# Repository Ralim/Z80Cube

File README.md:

# Z80Cube - Project Zeta
A 5 layer 5cm * 5cm cubish shaped z80 machine
Basically designed as a learning experience.
Big difference from other builds I have seen is the entire system runs on a 64K memory space of ram, and the atmega2560 pre-load's the bootloader into the chip on system startup.
This bootloader for the z80 then allows the user to test memory and load + execute programs.

## Layers
* Bus Display ->Led indicators for the bus
* Z80 CPU
* 64K SRAM/ROM
* Power and Programmer (Atmega 2560+flash storage to store the software)

##ToDo:
Basically everything
* Build PCBs
* Test PCBs
* Write the code for the bootloader (Going to use Arduino to keep it easy for others)
* Write arduino code for storing program packages
* Write arduino code for monitoring the bus
* write arduino code for single stepping operation

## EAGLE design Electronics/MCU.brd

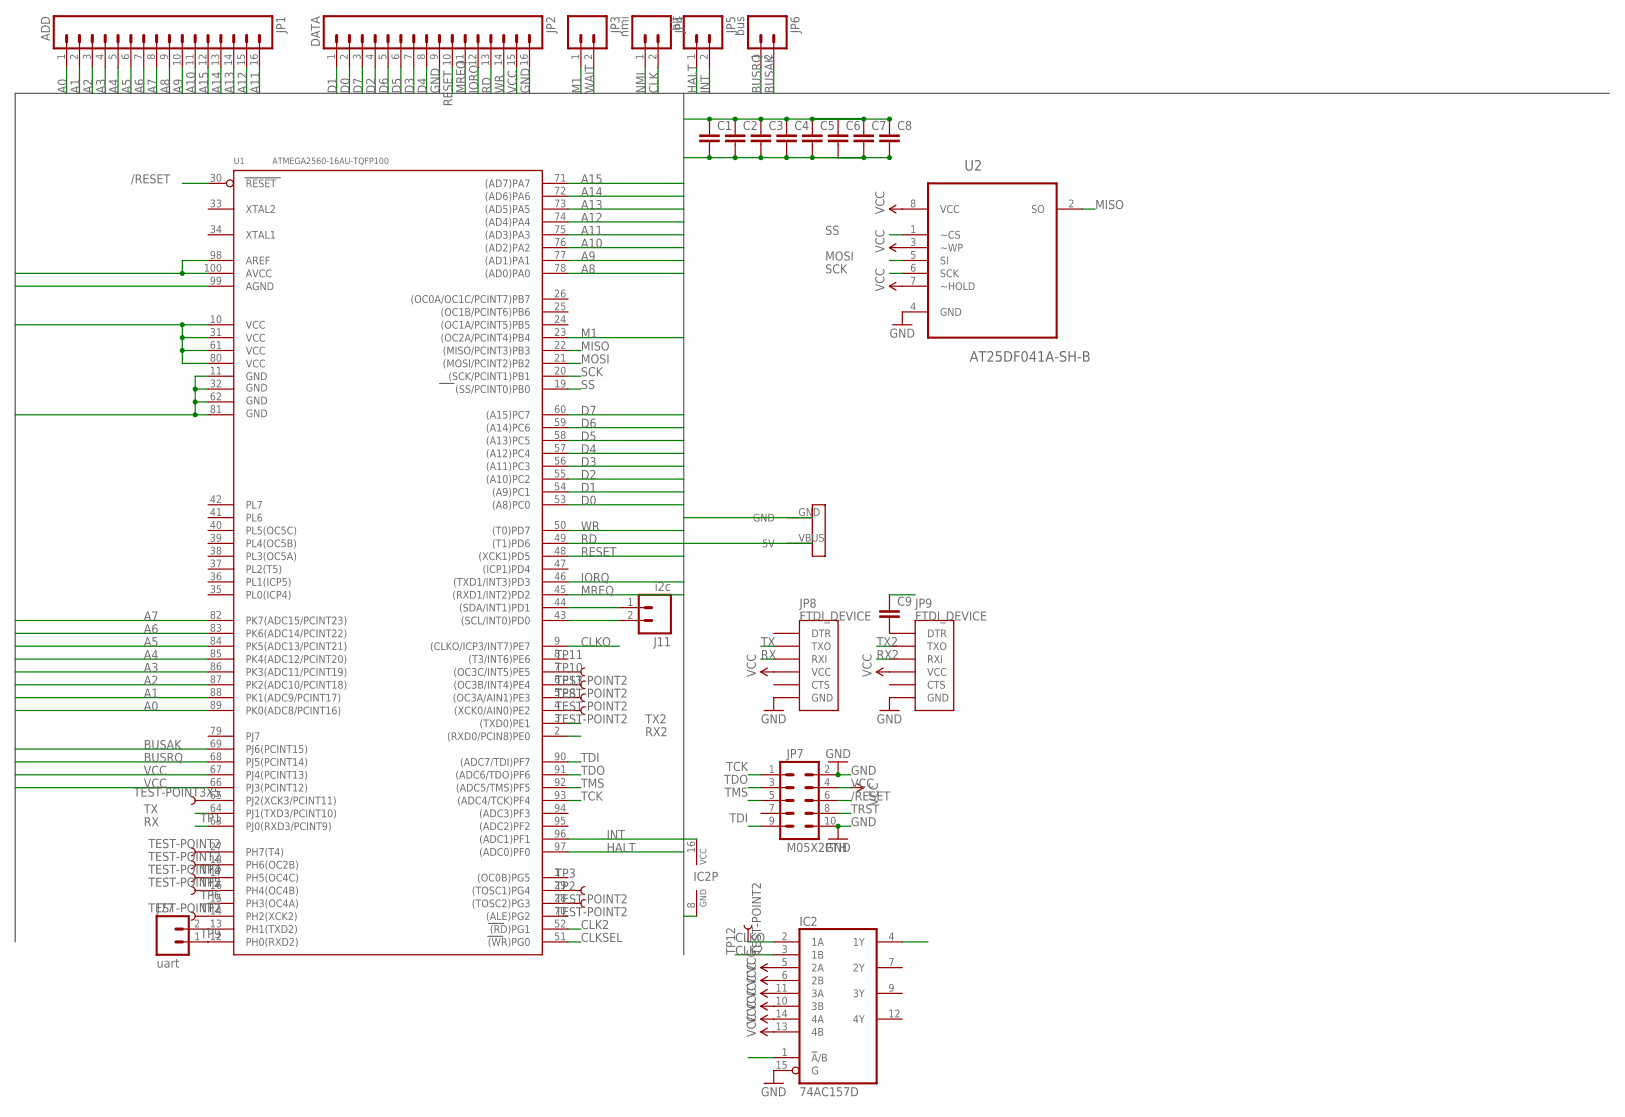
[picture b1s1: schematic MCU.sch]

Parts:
C1, C2, C3, C4, C5, C6, C7, C8, C9: C-EUC0805; C0805
IC2: 74AC157D; SO16
J11: i2c; 1X02
J77: uart; 1X02
JP1: ADD; 1X16
JP2: DATA; 1X16
JP3: M02PTH; 1X02
JP4: nmi; 1X02
JP5: hlt; 1X02
JP6: bus; 1X02
JP7: M05X2PTH; AVR_ICSP
JP8, JP9: FTDI_DEVICE; FTDI_DEVICE_SIDE
TP1: TEST-POINT3X5; PAD.03X.05
TP2, TP3, TP4, TP5, TP6, TP7, TP8, TP9, TP10, TP11, TP12, TP13: TEST-POINT2; PAD.02X.02
U1: ATMEGA2560-16AU-TQFP100; TQFP100-0.5-14X14MM
U2: AT25DF041A-SH-B; SOIC127P798X216-8N
U$1: USB-MICRO-PWR; USB-MICROB-PWR

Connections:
/RESET: C9.1, JP7.6, U1.30 (RESET)
A0: JP1.1, U1.89 (PK0(ADC8/PCINT16))
A1: JP1.2, U1.88 (PK1(ADC9/PCINT17))
A2: JP1.3, U1.87 (PK2(ADC10/PCINT18))
A3: JP1.4, U1.86 (PK3(ADC11/PCINT19))
A4: JP1.5, U1.85 (PK4(ADC12/PCINT20))
A5: JP1.6, U1.84 (PK5(ADC13/PCINT21))
A6: JP1.7, U1.83 (PK6(ADC14/PCINT22))
A7: JP1.8, U1.82 (PK7(ADC15/PCINT23))
A8: JP1.9, U1.78 ((AD0)PA0)
A9: JP1.10, U1.77 ((AD1)PA1)
A10: JP1.11, U1.76 ((AD2)PA2)
A11: JP1.16, U1.75 ((AD3)PA3)
A12: JP1.15, U1.74 ((AD4)PA4)
A13: JP1.14, U1.73 ((AD5)PA5)
A14: JP1.13, U1.72 ((AD6)PA6)
A15: JP1.12, U1.71 ((AD7)PA7)
BUSAK: JP6.2, U1.69 (PJ6(PCINT15))
BUSRQ: JP6.1, U1.68 (PJ5(PCINT14))
CLK: IC2.4 (1Y), JP4.2
CLK2: IC2.3 (1B), U1.52 ((RD)PG1)
CLKO: IC2.2 (1A), TP12.P$1, U1.9 ((CLKO/ICP3/INT7)PE7)
CLKSEL: IC2.1 (!A!/B), U1.51 ((WR)PG0)
D0: JP2.2, U1.53 ((A8)PC0)
D1: JP2.1, U1.54 ((A9)PC1)
D2: JP2.4, U1.55 ((A10)PC2)
D3: JP2.7, U1.56 ((A11)PC3)
D4: JP2.8, U1.57 ((A12)PC4)
D5: JP2.6, U1.58 ((A13)PC5)
D6: JP2.5, U1.59 ((A14)PC6)
D7: JP2.3, U1.60 ((A15)PC7)
GND: C1.2, C2.2, C3.2, C4.2, C5.2, C6.2, C7.2, C8.2, IC2.8 (GND), IC2.15 (G), JP2.9, JP2.16, JP7.2, JP7.10, JP8.P$6 (GND), JP9.P$6 (GND), U1.11 (GND), U1.32 (GND1), U1.62 (GND2), U1.81 (GND3), U1.99 (AGND), U2.4 (GND), U$1.GND
HALT: JP5.1, U1.97 ((ADC0)PF0)
INT: JP5.2, U1.96 ((ADC1)PF1)
IORQ: JP2.12, U1.46 ((TXD1/INT3)PD3)
M1: JP3.1, U1.23 ((OC2A/PCINT4)PB4)
MISO: U1.22 ((MISO/PCINT3)PB3), U2.2 (SO)
MOSI: U1.21 ((MOSI/PCINT2)PB2), U2.5 (SI)
MREQ: JP2.11, U1.45 ((RXD1/INT2)PD2)
unnamed: J77.1, U1.12 (PH0(RXD2))
unnamed: J77.2, U1.13 (PH1(TXD2))
unnamed: J11.1, U1.44 ((SDA/INT1)PD1)
unnamed: J11.2, U1.43 ((SCL/INT0)PD0)
unnamed: TP1.P$1, U1.65 (PJ2(XCK3/PCINT11))
unnamed: TP2.P$1, U1.28 ((TOSC2)PG3)
unnamed: TP3.P$1, U1.29 ((TOSC1)PG4)
unnamed: TP4.P$1, U1.27 (PH7(T4))
unnamed: TP5.P$1, U1.18 (PH6(OC2B))
unnamed: TP6.P$1, U1.17 (PH5(OC4C))
unnamed: TP7.P$1, U1.16 (PH4(OC4B))
unnamed: TP8.P$1, U1.4 ((XCK0/AIN0)PE2)
unnamed: TP9.P$1, U1.14 (PH2(XCK2))
unnamed: TP10.P$1, U1.6 ((OC3B/INT4)PE4)
unnamed: TP11.P$1, U1.7 ((OC3C/INT5)PE5)
unnamed: C9.2, JP9.P$1 (DTR)
unnamed: TP13.P$1, U1.5 ((OC3A/AIN1)PE3)
NMI: JP4.1
RD: JP2.13, U1.49 ((T1)PD6)
RESET: JP2.10, U1.48 ((XCK1)PD5)
RX: JP8.P$3 (RXI), U1.63 (PJ0(RXD3/PCINT9))
RX2: JP9.P$3 (RXI), U1.2 ((RXD0/PCIN8)PE0)
SCK: U1.20 ((SCK/PCINT1)PB1), U2.6 (SCK)
SS: U1.19 ((SS/PCINT0)PB0), U2.1 (~CS)
TCK: JP7.1, U1.93 ((ADC4/TCK)PF4)
TDI: JP7.9, U1.90 ((ADC7/TDI)PF7)
TDO: JP7.3, U1.91 ((ADC6/TDO)PF6)
TMS: JP7.5, U1.92 ((ADC5/TMS)PF5)
TRST: JP7.8
TX: JP8.P$2 (TXO), U1.64 (PJ1(TXD3/PCINT10))
TX2: JP9.P$2 (TXO), U1.3 ((TXD0)PE1)
VCC: C1.1, C2.1, C3.1, C4.1, C5.1, C6.1, C7.1, C8.1, IC2.5 (2A), IC2.6 (2B), IC2.10 (3B), IC2.11 (3A), IC2.13 (4B), IC2.14 (4A), IC2.16 (VCC), JP2.15, JP7.4, JP8.P$4 (VCC), JP9.P$4 (VCC), U1.10 (VCC), U1.31 (VCC1), U1.61 (VCC2), U1.66 (PJ3(PCINT12)), U1.67 (PJ4(PCINT13)), U1.80 (VCC3), U1.98 (AREF), U1.100 (AVCC), U2.3 (~WP), U2.7 (~HOLD), U2.8 (VCC), U$1.VBUS (5V)
WAIT: JP3.2
WR: JP2.14, U1.50 ((T0)PD7)

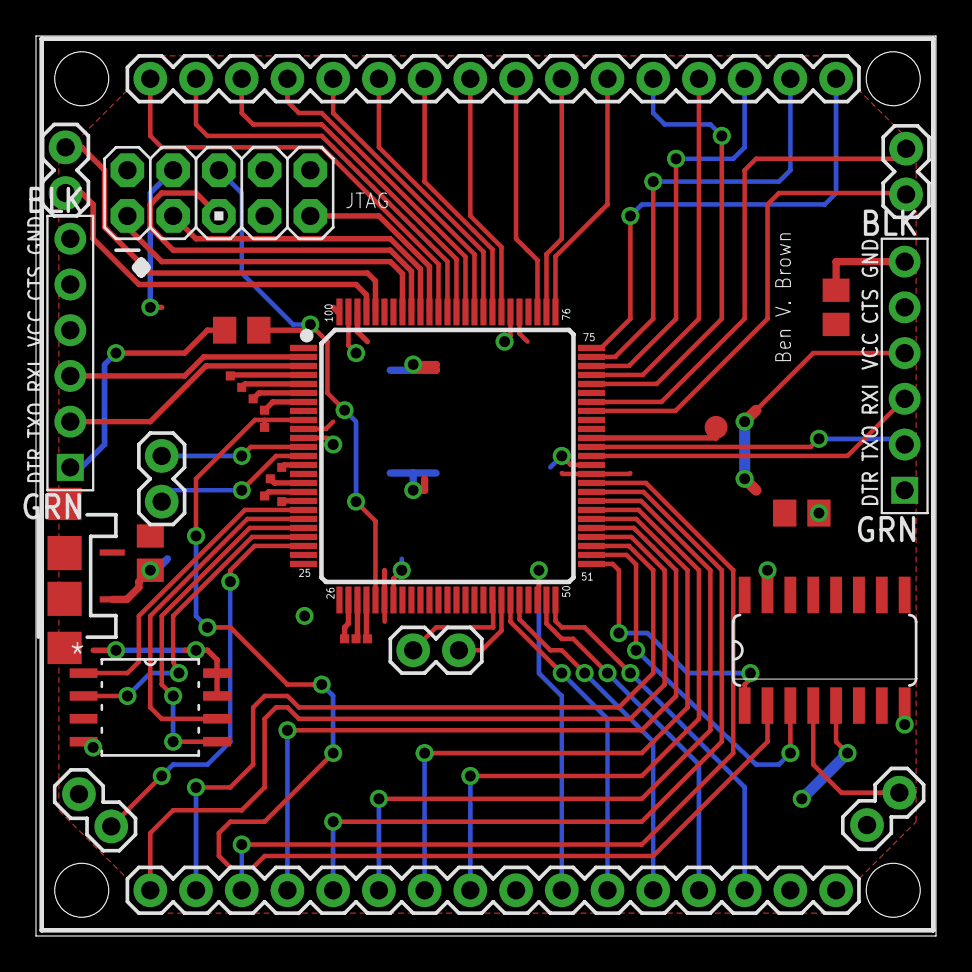
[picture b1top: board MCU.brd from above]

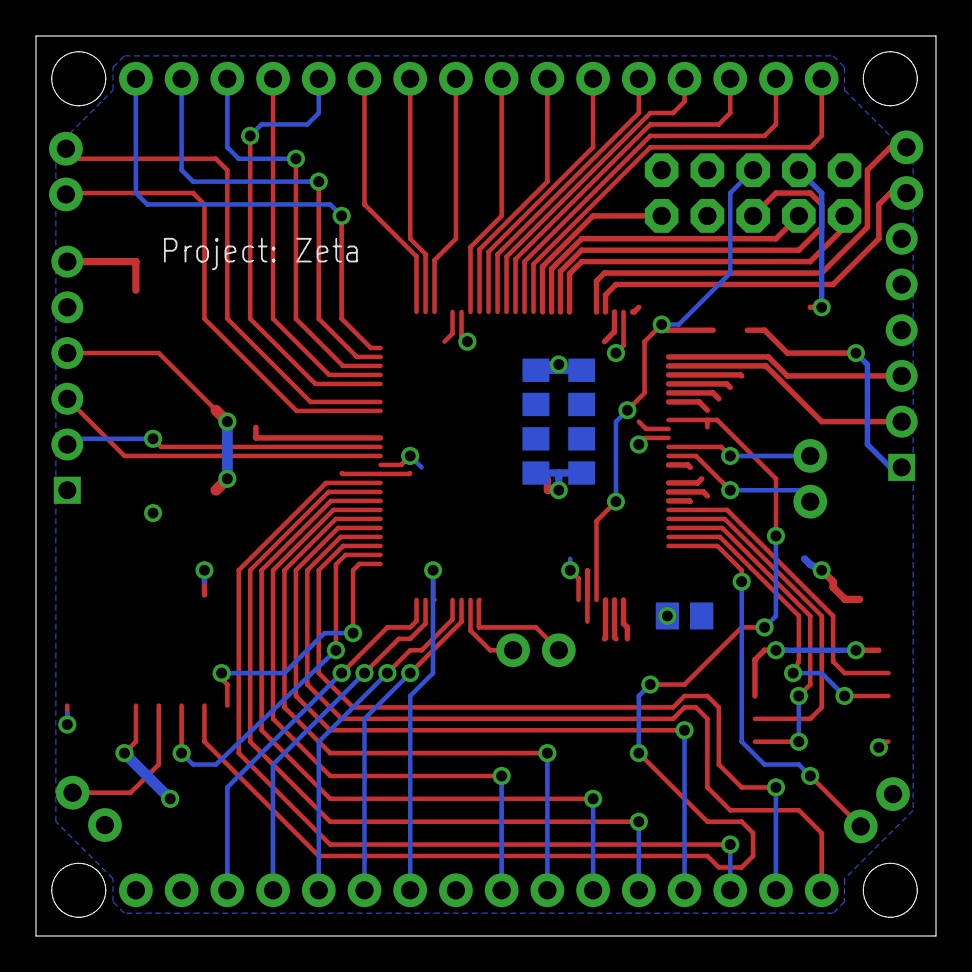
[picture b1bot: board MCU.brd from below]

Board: 2 copper layers, 50.0 x 50.0 mm, 37 parts (5 on the bottom side), 70 nets.

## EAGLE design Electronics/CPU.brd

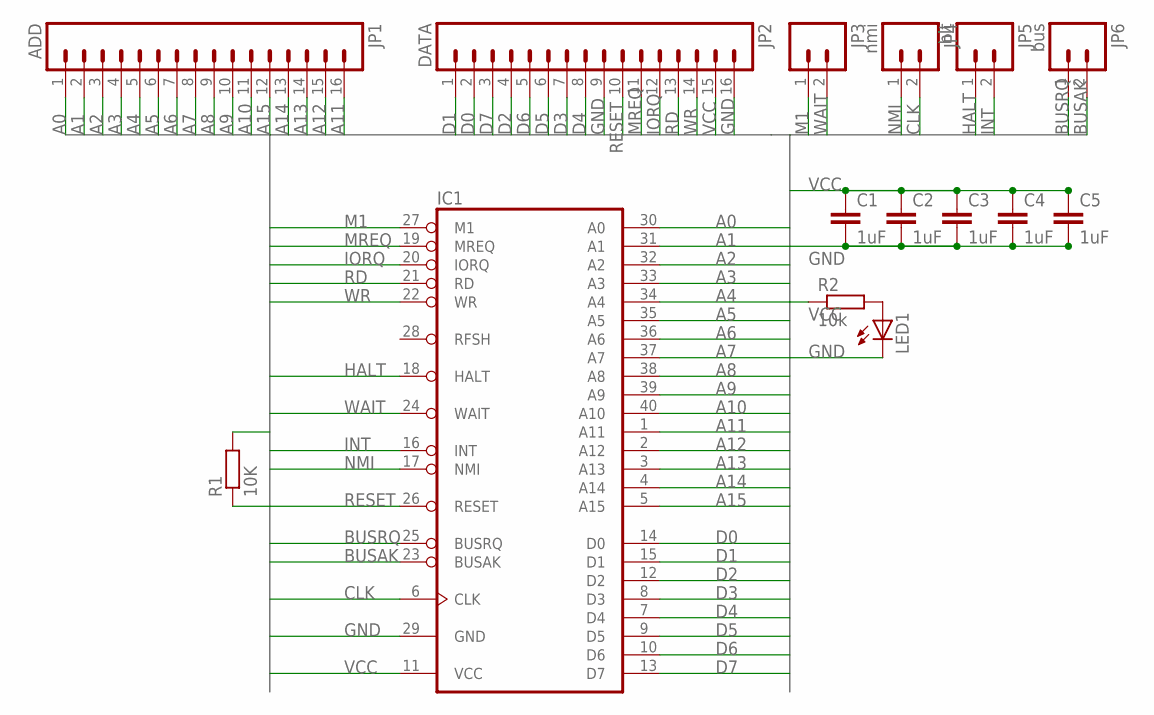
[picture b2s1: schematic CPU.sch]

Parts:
C1, C2, C3, C4, C5: 1uF; C0805
IC1: Z80CPU; DIL40
JP1: ADD; 1X16
JP2: DATA; 1X16
JP3: M02PTH; 1X02
JP4: nmi; 1X02
JP5: hlt; 1X02
JP6: bus; 1X02
LED1: LEDCHIP-LED0805; CHIP-LED0805
R1: 10K; M0805
R2: 10k; M0805

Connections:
A0: IC1.30 (A0), JP1.1
A1: IC1.31 (A1), JP1.2
A2: IC1.32 (A2), JP1.3
A3: IC1.33 (A3), JP1.4
A4: IC1.34 (A4), JP1.5
A5: IC1.35 (A5), JP1.6
A6: IC1.36 (A6), JP1.7
A7: IC1.37 (A7), JP1.8
A8: IC1.38 (A8), JP1.9
A9: IC1.39 (A9), JP1.10
A10: IC1.40 (A10), JP1.11
A11: IC1.1 (A11), JP1.16
A12: IC1.2 (A12), JP1.15
A13: IC1.3 (A13), JP1.14
A14: IC1.4 (A14), JP1.13
A15: IC1.5 (A15), JP1.12
BUSAK: IC1.23 (BUSAK), JP6.2
BUSRQ: IC1.25 (BUSRQ), JP6.1
CLK: IC1.6 (CLK), JP4.2
D0: IC1.14 (D0), JP2.2
D1: IC1.15 (D1), JP2.1
D2: IC1.12 (D2), JP2.4
D3: IC1.8 (D3), JP2.7
D4: IC1.7 (D4), JP2.8
D5: IC1.9 (D5), JP2.6
D6: IC1.10 (D6), JP2.5
D7: IC1.13 (D7), JP2.3
GND: C1.2, C2.2, C3.2, C4.2, C5.2, IC1.29 (GND), JP2.9, JP2.16, LED1.C
HALT: IC1.18 (HALT), JP5.1
INT: IC1.16 (INT), JP5.2
IORQ: IC1.20 (IORQ), JP2.12
M1: IC1.27 (M1), JP3.1
MREQ: IC1.19 (MREQ), JP2.11
unnamed: LED1.A, R2.2
NMI: IC1.17 (NMI), JP4.1
RD: IC1.21 (RD), JP2.13
RESET: IC1.26 (RESET), JP2.10, R1.1
VCC: C1.1, C2.1, C3.1, C4.1, C5.1, IC1.11 (VCC), JP2.15, R1.2, R2.1
WAIT: IC1.24 (WAIT), JP3.2
WR: IC1.22 (WR), JP2.14

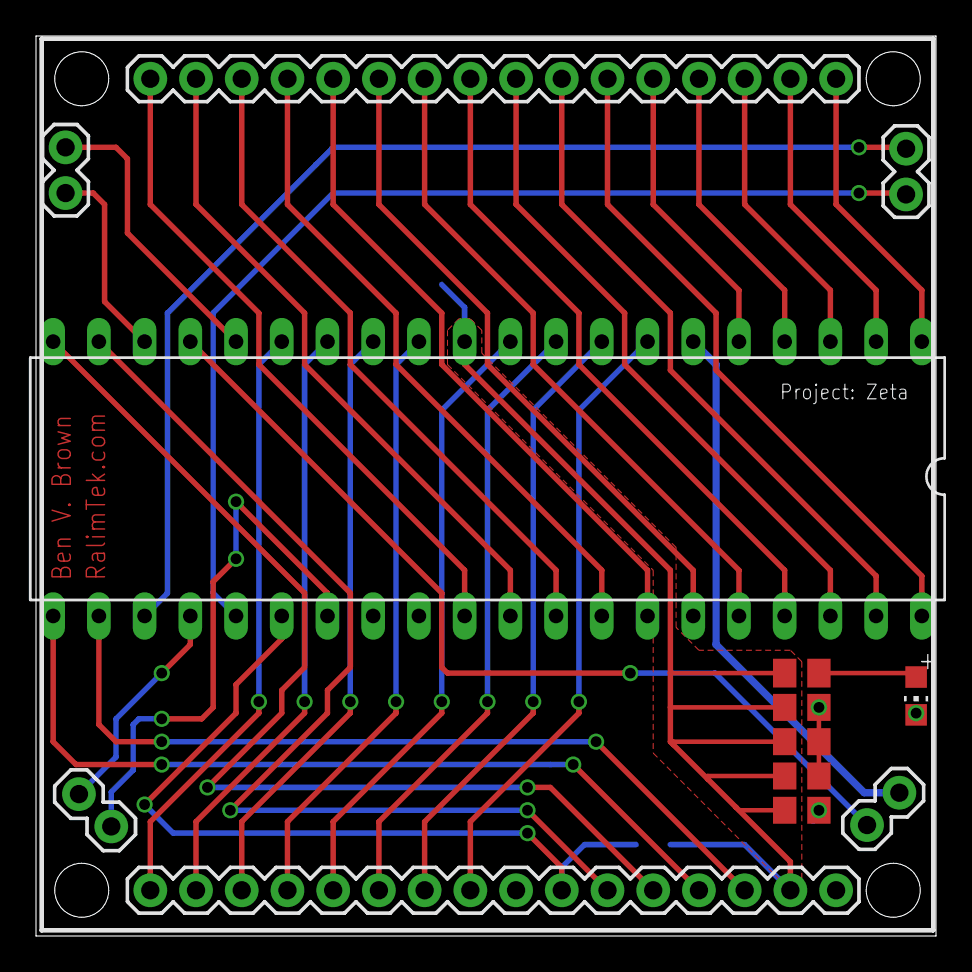
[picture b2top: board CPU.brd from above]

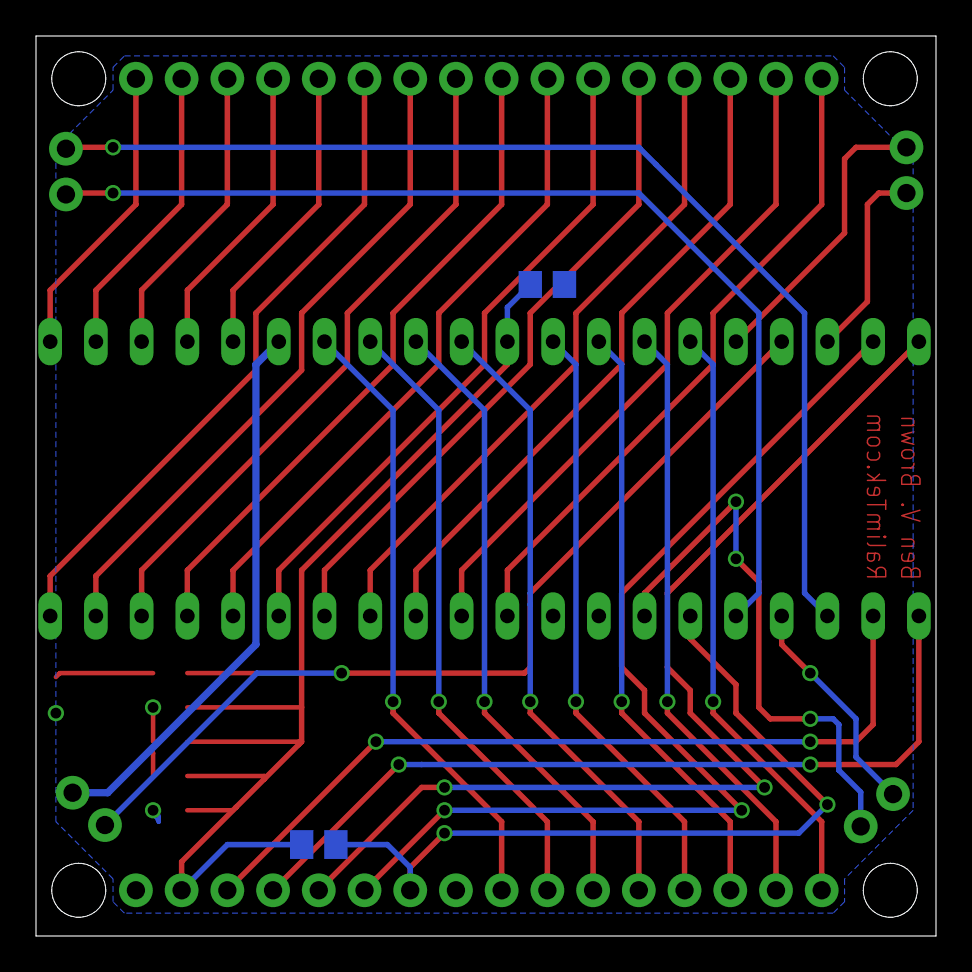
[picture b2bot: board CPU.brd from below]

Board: 2 copper layers, 50.0 x 50.0 mm, 15 parts (2 on the bottom side), 40 nets.

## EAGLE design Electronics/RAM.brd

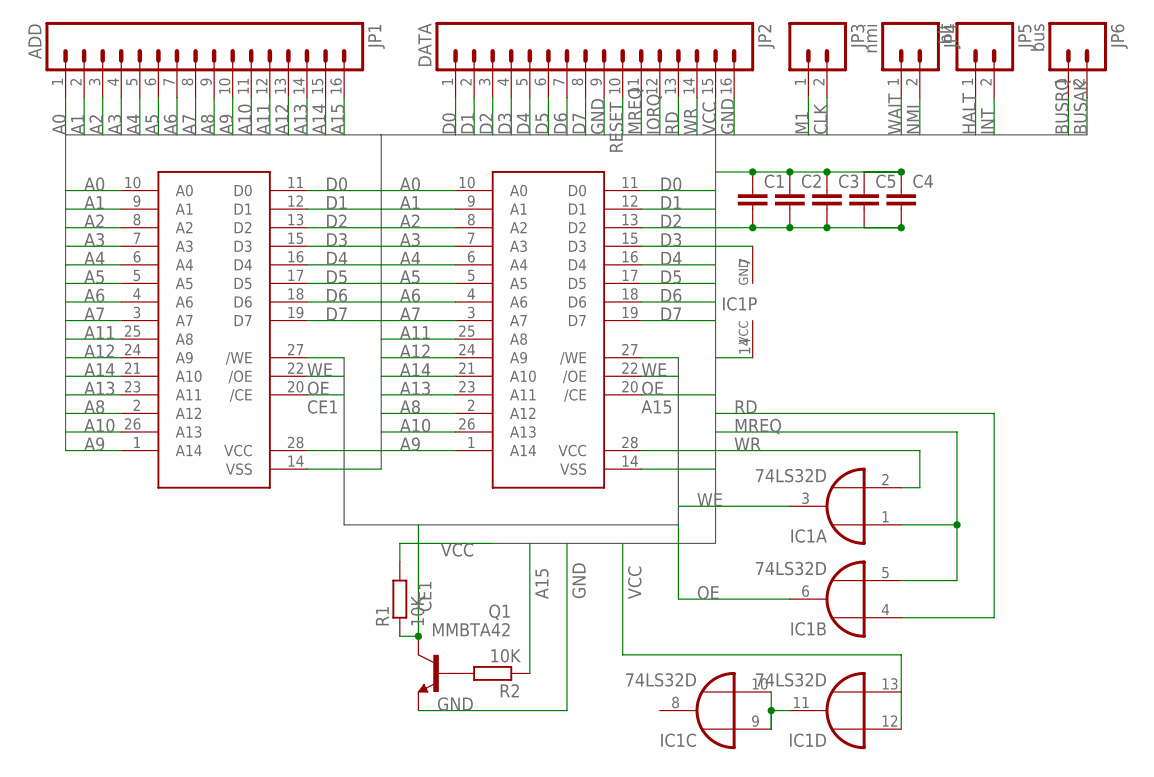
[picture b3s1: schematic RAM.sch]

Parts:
C1, C2, C3, C4, C5: C-EUC0805; C0805
IC1: 74LS32D; SO14
JP1: ADD; 1X16
JP2: DATA; 1X16
JP3: M02PTH; 1X02
JP4: nmi; 1X02
JP5: hlt; 1X02
JP6: bus; 1X02
Q1: MMBTA42; SOT23
R1, R2: 10K; M0805
U$1, U$2: AS7C256; SOP28

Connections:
A0: JP1.1, U$1.10 (A0), U$2.10 (A0)
A1: JP1.2, U$1.9 (A1), U$2.9 (A1)
A2: JP1.3, U$1.8 (A2), U$2.8 (A2)
A3: JP1.4, U$1.7 (A3), U$2.7 (A3)
A4: JP1.5, U$1.6 (A4), U$2.6 (A4)
A5: JP1.6, U$1.5 (A5), U$2.5 (A5)
A6: JP1.7, U$1.4 (A6), U$2.4 (A6)
A7: JP1.8, U$1.3 (A7), U$2.3 (A7)
A8: JP1.9, U$1.2 (A12), U$2.2 (A12)
A9: JP1.10, U$1.1 (A14), U$2.1 (A14)
A10: JP1.11, U$1.26 (A13), U$2.26 (A13)
A11: JP1.12, U$1.25 (A8), U$2.25 (A8)
A12: JP1.13, U$1.24 (A9), U$2.24 (A9)
A13: JP1.14, U$1.23 (A11), U$2.23 (A11)
A14: JP1.15, U$1.21 (A10), U$2.21 (A10)
A15: JP1.16, R2.1, U$2.20 (/CE)
BUSAK: JP6.2
BUSRQ: JP6.1
CE1: Q1.3 (C), R1.1, U$1.20 (/CE)
CLK: JP3.2
D0: JP2.1, U$1.11 (D0), U$2.11 (D0)
D1: JP2.2, U$1.12 (D1), U$2.12 (D1)
D2: JP2.3, U$1.13 (D2), U$2.13 (D2)
D3: JP2.4, U$1.15 (D3), U$2.15 (D3)
D4: JP2.5, U$1.16 (D4), U$2.16 (D4)
D5: JP2.6, U$1.17 (D5), U$2.17 (D5)
D6: JP2.7, U$1.18 (D6), U$2.18 (D6)
D7: JP2.8, U$1.19 (D7), U$2.19 (D7)
GND: C1.2, C2.2, C3.2, C4.2, C5.2, IC1.7 (GND), JP2.9, JP2.16, Q1.2 (E), U$1.14 (VSS), U$2.14 (VSS)
HALT: JP5.1
INT: JP5.2
IORQ: JP2.12
M1: JP3.1
MREQ: IC1.1 (I0), IC1.5 (I1), JP2.11
unnamed: IC1.9 (I0), IC1.10 (I1), IC1.11 (O)
unnamed: Q1.1 (B), R2.2
NMI: JP4.2
OE: IC1.6 (O), U$1.22 (/OE), U$2.22 (/OE)
RD: IC1.4 (I0), JP2.13
RESET: JP2.10
VCC: C1.1, C2.1, C3.1, C4.1, C5.1, IC1.12 (I0), IC1.13 (I1), IC1.14 (VCC), JP2.15, R1.2, U$1.28 (VCC), U$2.28 (VCC)
WAIT: JP4.1
WE: IC1.3 (O), U$1.27 (/WE), U$2.27 (/WE)
WR: IC1.2 (I1), JP2.14

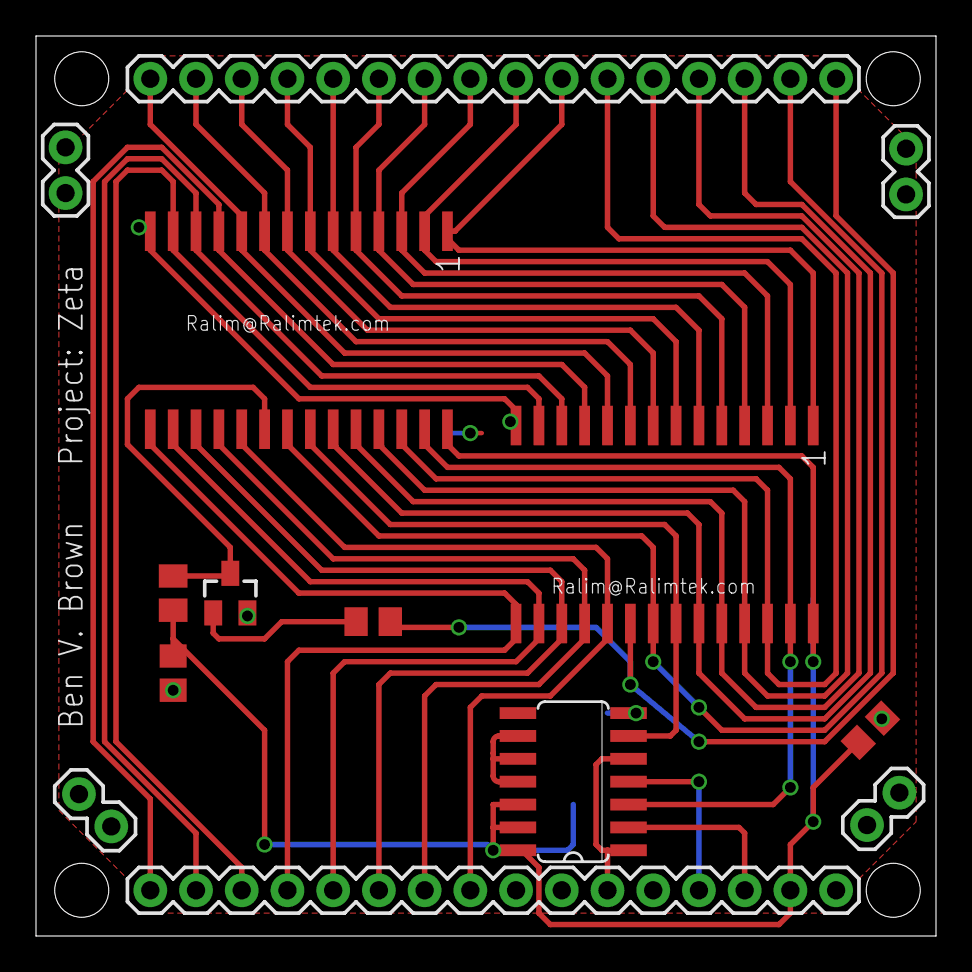
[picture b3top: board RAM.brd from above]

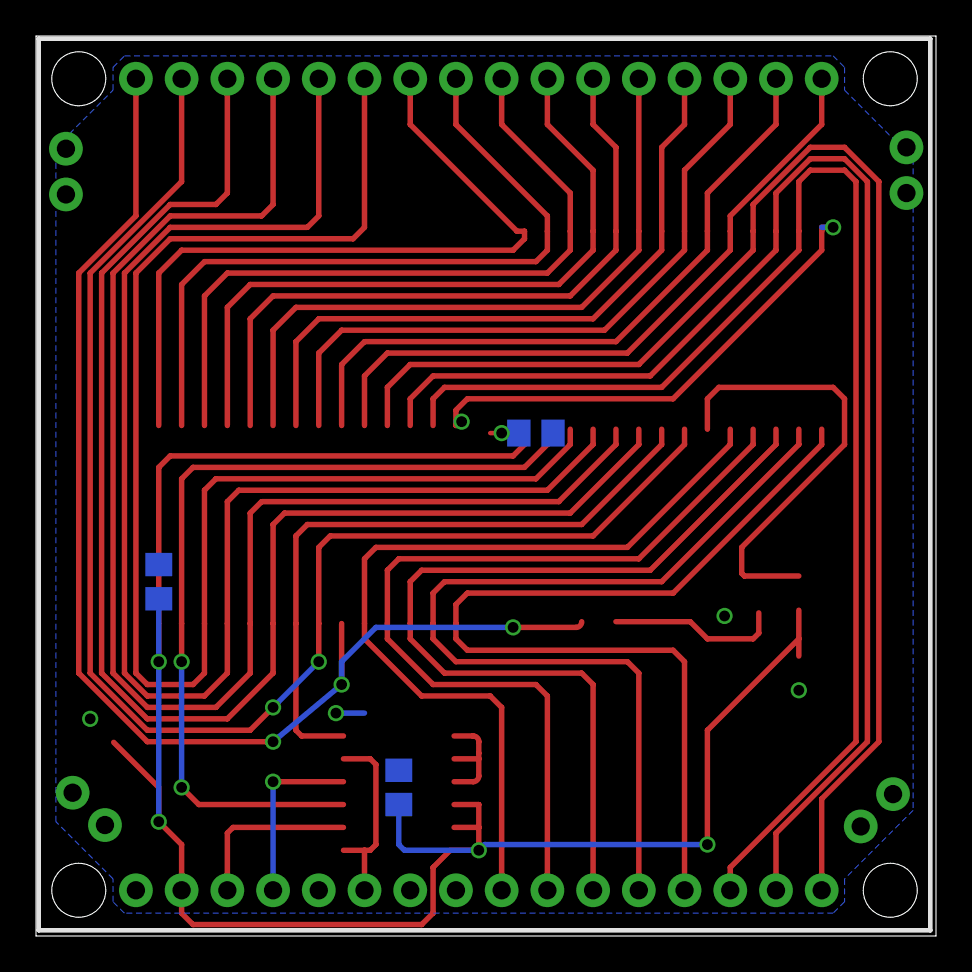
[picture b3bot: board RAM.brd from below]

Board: 2 copper layers, 50.0 x 50.0 mm, 17 parts (3 on the bottom side), 34 nets.

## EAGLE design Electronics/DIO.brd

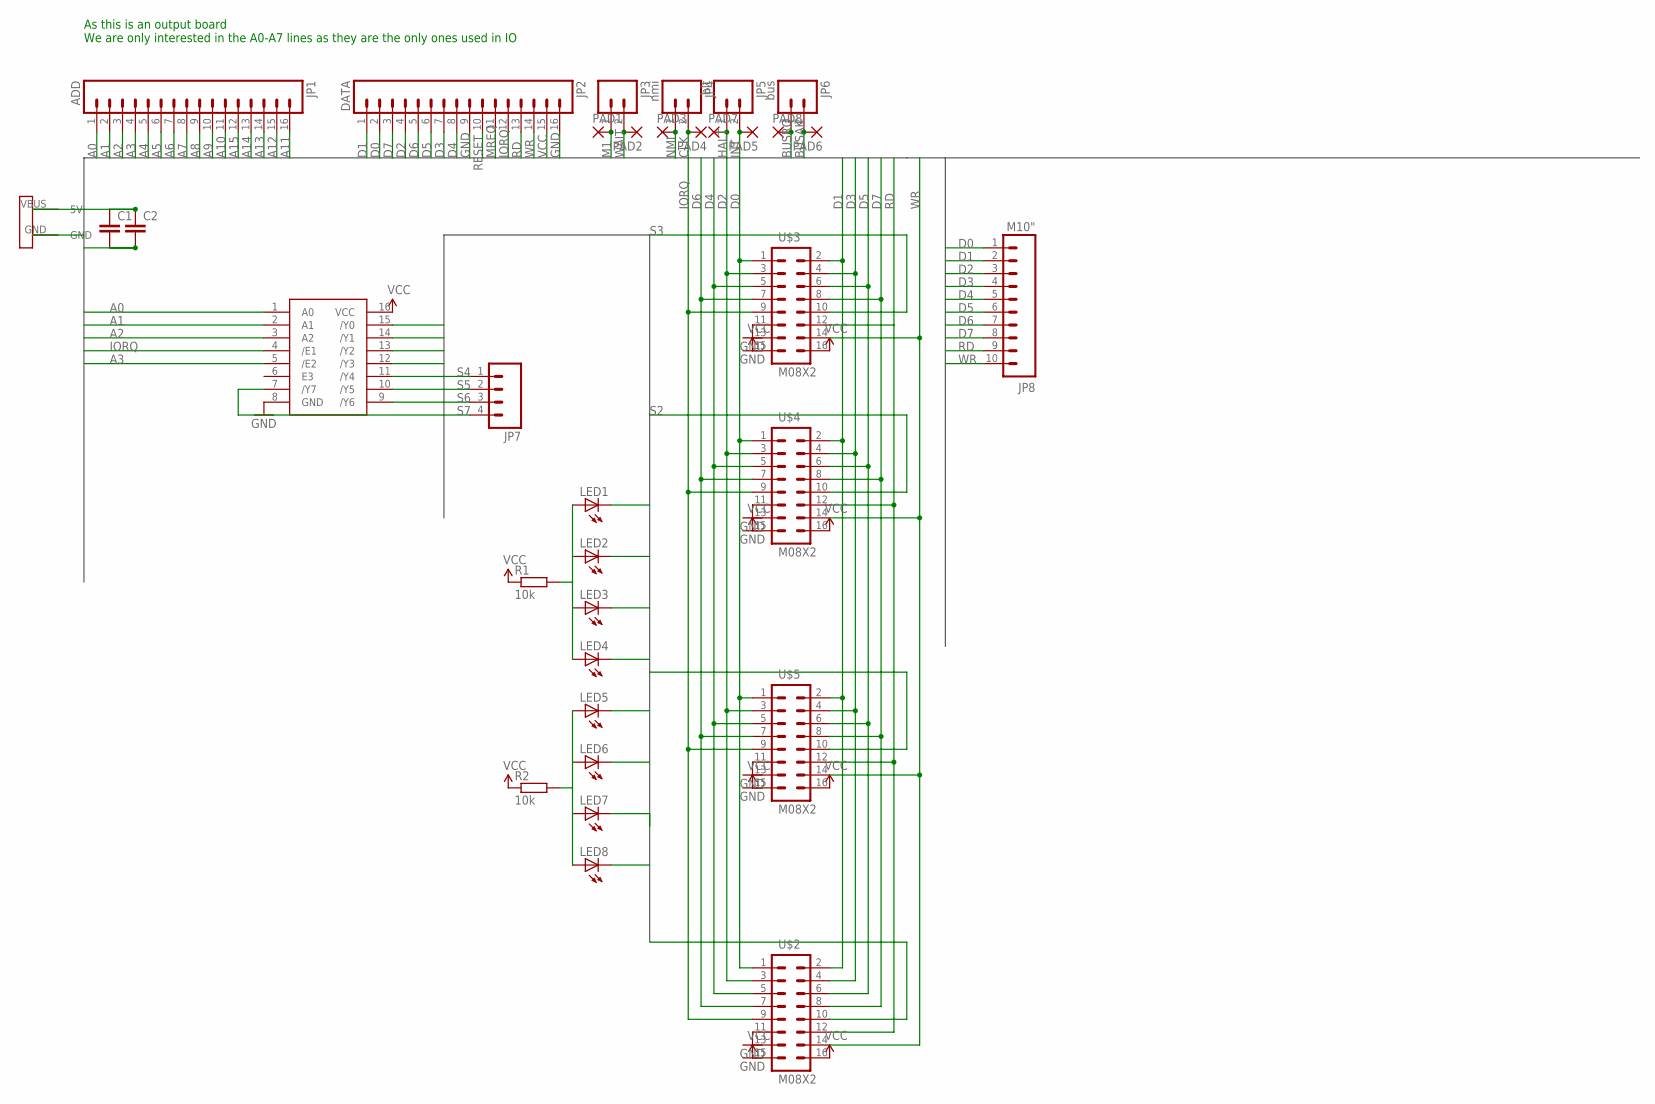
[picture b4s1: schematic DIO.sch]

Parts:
C1, C2: C-EUC0805; C0805
JP1: ADD; 1X16
JP2: DATA; 1X16
JP3: M02PTH; 1X02
JP4: nmi; 1X02
JP5: hlt; 1X02
JP6: bus; 1X02
JP7: M04PTH; 1X04
JP8: M10"; 1X10
LED1, LED2, LED3, LED4, LED5, LED6, LED7, LED8: LEDCHIP-LED0805; CHIP-LED0805
PAD1, PAD2, PAD3, PAD4, PAD5, PAD6, PAD7, PAD8: SMD2; SMD1,27-2,54
R1, R2: 10k; M0805
U$1: 74LVC138AD; SO016
U$2, U$3, U$4, U$5: M08X2; 2X8
U$6: USB-MICRO-PWR; USB-MICROB-PWR

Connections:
A0: JP1.1, U$1.1 (A0)
A1: JP1.2, U$1.2 (A1)
A2: JP1.3, U$1.3 (A2)
A3: JP1.4, U$1.5 (/E2)
A4: JP1.5
A5: JP1.6
A6: JP1.7
A7: JP1.8
A8: JP1.9
A9: JP1.10
A10: JP1.11
A11: JP1.16
A12: JP1.15
A13: JP1.14
A14: JP1.13
A15: JP1.12
BUSAK: JP6.2, PAD6.1
BUSRQ: JP6.1, PAD8.1
CLK: JP4.2, PAD4.1
D0: JP2.2, JP8.1, U$2.1, U$3.1, U$4.1, U$5.1
D1: JP2.1, JP8.2, U$2.2, U$3.2, U$4.2, U$5.2
D2: JP2.4, JP8.3, U$2.3, U$3.3, U$4.3, U$5.3
D3: JP2.7, JP8.4, U$2.4, U$3.4, U$4.4, U$5.4
D4: JP2.8, JP8.5, U$2.5, U$3.5, U$4.5, U$5.5
D5: JP2.6, JP8.6, U$2.6, U$3.6, U$4.6, U$5.6
D6: JP2.5, JP8.7, U$2.7, U$3.7, U$4.7, U$5.7
D7: JP2.3, JP8.8, U$2.8, U$3.8, U$4.8, U$5.8
GND: C1.2, C2.2, JP2.9, JP2.16, U$1.8 (GND), U$2.11, U$2.13, U$3.11, U$3.13, U$4.11, U$4.13, U$5.11, U$5.13, U$6.GND
HALT: JP5.1, PAD7.1
INT: JP5.2, PAD5.1
IORQ: JP2.12, U$1.4 (/E1), U$2.9, U$3.9, U$4.9, U$5.9
M1: JP3.1, PAD1.1
MREQ: JP2.11
unnamed: LED1.A, LED2.A, LED3.A, LED4.A, R1.2
unnamed: LED5.A, LED6.A, LED7.A, LED8.A, R2.2
NMI: JP4.1, PAD3.1
RD: JP2.13, JP8.9, U$2.12, U$3.12, U$4.12, U$5.12
RESET: JP2.10
S0: LED1.C, U$1.15 (/Y0), U$2.10
S1: LED2.C, U$1.14 (/Y1), U$5.10
S2: LED3.C, U$1.13 (/Y2), U$4.10
S3: LED4.C, U$1.12 (/Y3), U$3.10
S4: JP7.1, LED5.C, U$1.11 (/Y4)
S5: JP7.2, LED6.C, U$1.10 (/Y5)
S6: JP7.3, LED7.C, U$1.9 (/Y6)
S7: JP7.4, LED8.C, U$1.7 (/Y7)
VCC: C1.1, C2.1, JP2.15, R1.1, R2.1, U$1.16 (VCC), U$2.15, U$2.16, U$3.15, U$3.16, U$4.15, U$4.16, U$5.15, U$5.16, U$6.VBUS (5V)
WAIT: JP3.2, PAD2.1
WR: JP2.14, JP8.10, U$2.14, U$3.14, U$4.14, U$5.14

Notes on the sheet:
As this is an output board We are only interested in the A0-A7 lines as they are the only ones used in IO

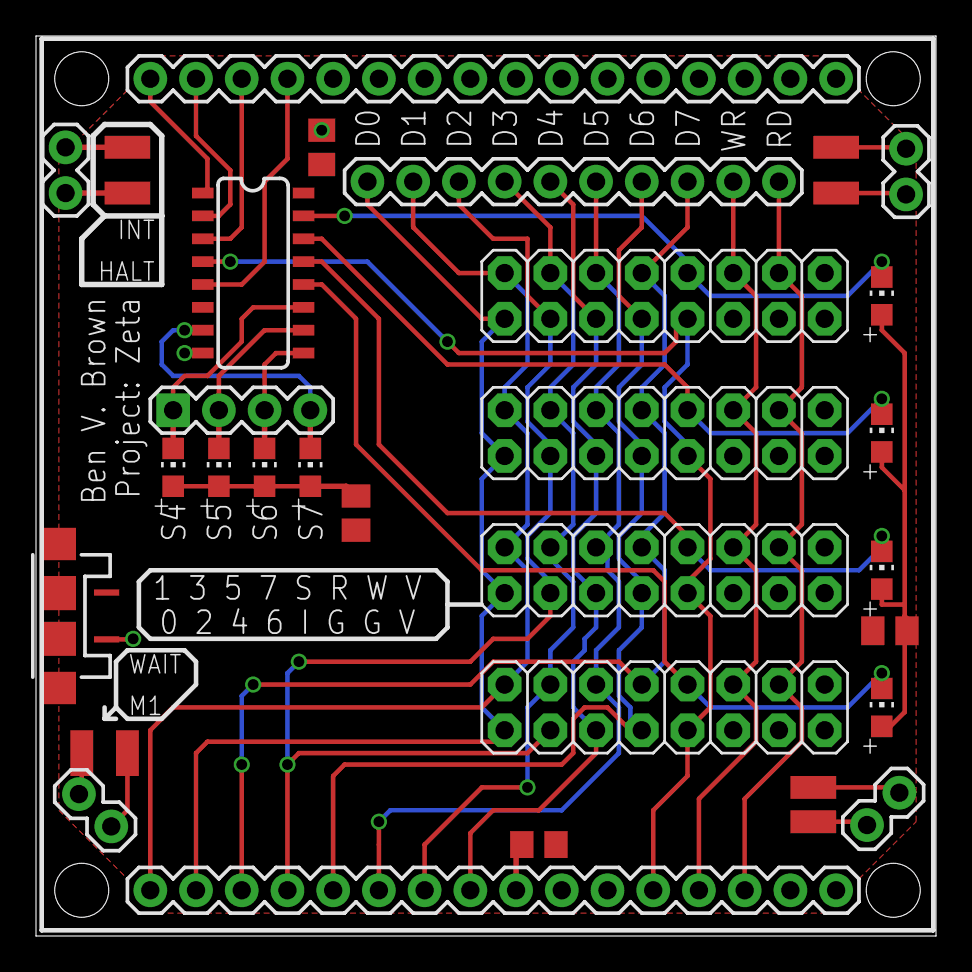
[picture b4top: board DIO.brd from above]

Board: 2 copper layers, 50.0 x 50.0 mm, 34 parts (0 on the bottom side), 35 nets.

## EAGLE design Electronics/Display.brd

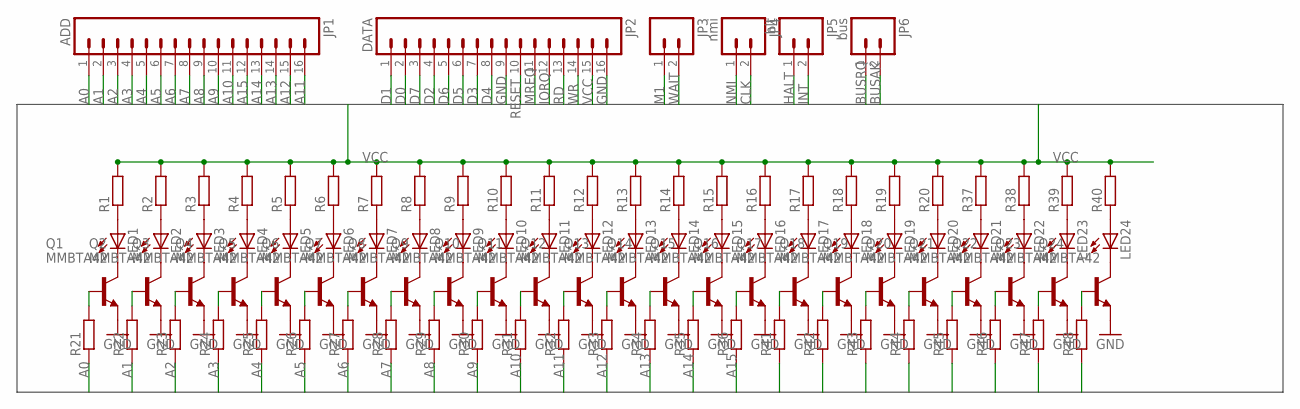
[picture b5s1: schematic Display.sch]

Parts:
JP1: ADD; 1X16
JP2: DATA; 1X16
JP3: M02PTH; 1X02
JP4: nmi; 1X02
JP5: hlt; 1X02
JP6: bus; 1X02
LED1, LED2, LED3, LED4, LED5, LED6, LED7, LED8, LED9, LED10, LED11, LED12, LED13, LED14, LED15, LED16, LED17, LED18, LED19, LED20, LED21, LED22, LED23, LED24: LEDCHIP-LED0805; CHIP-LED0805
Q1, Q2, Q3, Q4, Q5, Q6, Q7, Q8, Q9, Q10, Q11, Q12, Q13, Q14, Q15, Q16, Q17, Q18, Q19, Q20, Q21, Q22, Q23, Q24: MMBTA42; SOT23
R1, R2, R3, R4, R5, R6, R7, R8, R9, R10, R11, R12, R13, R14, R15, R16, R17, R18, R19, R20, R21, R22, R23, R24, R25, R26, R27, R28, R29, R30, R31, R32, R33, R34, R35, R36, R37, R38, R39, R40, R41, R42, R43, R44, R45, R46, R47, R48: R-EU_M0805; M0805

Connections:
A0: JP1.1, R21.1
A1: JP1.2, R22.1
A2: JP1.3, R23.1
A3: JP1.4, R24.1
A4: JP1.5, R25.1
A5: JP1.6, R26.1
A6: JP1.7, R27.1
A7: JP1.8, R28.1
A8: JP1.9, R29.1
A9: JP1.10, R30.1
A10: JP1.11, R31.1
A11: JP1.16, R32.1
A12: JP1.15, R33.1
A13: JP1.14, R34.1
A14: JP1.13, R35.1
A15: JP1.12, R36.1
BUSAK: JP6.2
BUSRQ: JP6.1
CLK: JP4.2
D0: JP2.2, R41.1
D1: JP2.1, R42.1
D2: JP2.4, R43.1
D3: JP2.7, R44.1
D4: JP2.8, R45.1
D5: JP2.6, R46.1
D6: JP2.5, R47.1
D7: JP2.3, R48.1
GND: JP2.9, JP2.16, Q1.2 (E), Q2.2 (E), Q3.2 (E), Q4.2 (E), Q5.2 (E), Q6.2 (E), Q7.2 (E), Q8.2 (E), Q9.2 (E), Q10.2 (E), Q11.2 (E), Q12.2 (E), Q13.2 (E), Q14.2 (E), Q15.2 (E), Q16.2 (E), Q17.2 (E), Q18.2 (E), Q19.2 (E), Q20.2 (E), Q21.2 (E), Q22.2 (E), Q23.2 (E), Q24.2 (E)
HALT: JP5.1
INT: JP5.2
IORQ: JP2.12
M1: JP3.1
MREQ: JP2.11
unnamed: LED1.A, R1.1
unnamed: LED1.C, Q1.3 (C)
unnamed: LED2.A, R2.1
unnamed: LED2.C, Q2.3 (C)
unnamed: LED3.A, R3.1
unnamed: LED3.C, Q3.3 (C)
unnamed: LED4.A, R4.1
unnamed: LED4.C, Q4.3 (C)
unnamed: LED5.A, R5.1
unnamed: LED5.C, Q5.3 (C)
unnamed: LED6.A, R6.1
unnamed: LED6.C, Q6.3 (C)
unnamed: LED7.A, R7.1
unnamed: LED7.C, Q7.3 (C)
unnamed: LED8.A, R8.1
unnamed: LED8.C, Q8.3 (C)
unnamed: LED9.A, R9.1
unnamed: LED9.C, Q9.3 (C)
unnamed: LED10.A, R10.1
unnamed: LED10.C, Q10.3 (C)
unnamed: LED11.A, R11.1
unnamed: LED11.C, Q11.3 (C)
unnamed: LED12.A, R12.1
unnamed: LED12.C, Q12.3 (C)
unnamed: LED13.A, R13.1
unnamed: LED13.C, Q13.3 (C)
unnamed: LED14.A, R14.1
unnamed: LED14.C, Q14.3 (C)
unnamed: LED15.A, R15.1
unnamed: LED15.C, Q15.3 (C)
unnamed: LED16.A, R16.1
unnamed: LED16.C, Q16.3 (C)
unnamed: Q24.1 (B), R48.2
unnamed: Q23.1 (B), R47.2
unnamed: Q22.1 (B), R46.2
unnamed: Q21.1 (B), R45.2
unnamed: Q20.1 (B), R44.2
unnamed: Q19.1 (B), R43.2
unnamed: Q18.1 (B), R42.2
unnamed: Q17.1 (B), R41.2
unnamed: LED17.A, R17.1
unnamed: LED17.C, Q17.3 (C)
unnamed: LED18.A, R18.1
unnamed: LED18.C, Q18.3 (C)
unnamed: Q16.1 (B), R36.2
unnamed: Q15.1 (B), R35.2
unnamed: Q14.1 (B), R34.2
unnamed: Q13.1 (B), R33.2
unnamed: Q12.1 (B), R32.2
unnamed: Q11.1 (B), R31.2
unnamed: Q10.1 (B), R30.2
unnamed: Q9.1 (B), R29.2
unnamed: Q8.1 (B), R28.2
unnamed: Q7.1 (B), R27.2
unnamed: Q6.1 (B), R26.2
unnamed: Q5.1 (B), R25.2
unnamed: Q4.1 (B), R24.2
unnamed: Q3.1 (B), R23.2
unnamed: Q2.1 (B), R22.2
unnamed: Q1.1 (B), R21.2
unnamed: LED19.A, R19.1
unnamed: LED19.C, Q19.3 (C)
unnamed: LED20.A, R20.1
unnamed: LED20.C, Q20.3 (C)
unnamed: LED21.A, R37.1
unnamed: LED21.C, Q21.3 (C)
unnamed: LED22.A, R38.1
unnamed: LED22.C, Q22.3 (C)
unnamed: LED23.A, R39.1
unnamed: LED23.C, Q23.3 (C)
unnamed: LED24.A, R40.1
unnamed: LED24.C, Q24.3 (C)
NMI: JP4.1
RD: JP2.13
RESET: JP2.10
VCC: JP2.15, R1.2, R2.2, R3.2, R4.2, R5.2, R6.2, R7.2, R8.2, R9.2, R10.2, R11.2, R12.2, R13.2, R14.2, R15.2, R16.2, R17.2, R18.2, R19.2, R20.2, R37.2, R38.2, R39.2, R40.2
WAIT: JP3.2
WR: JP2.14

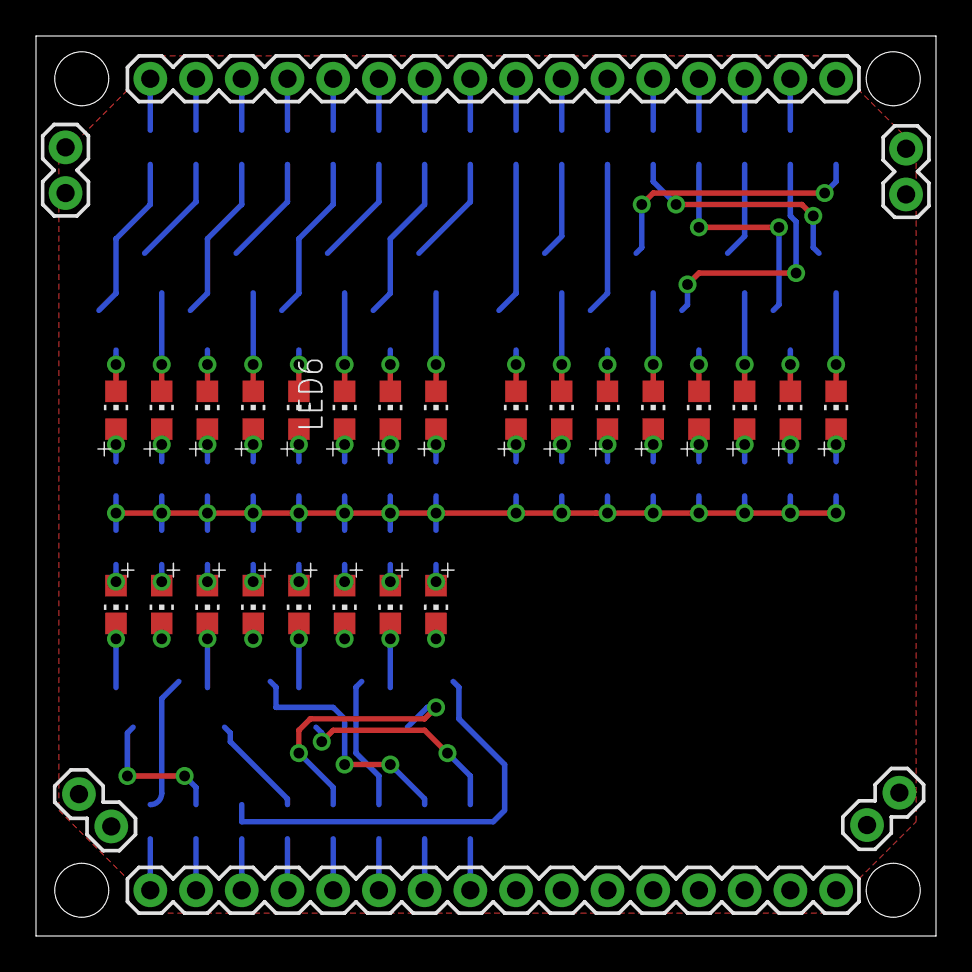
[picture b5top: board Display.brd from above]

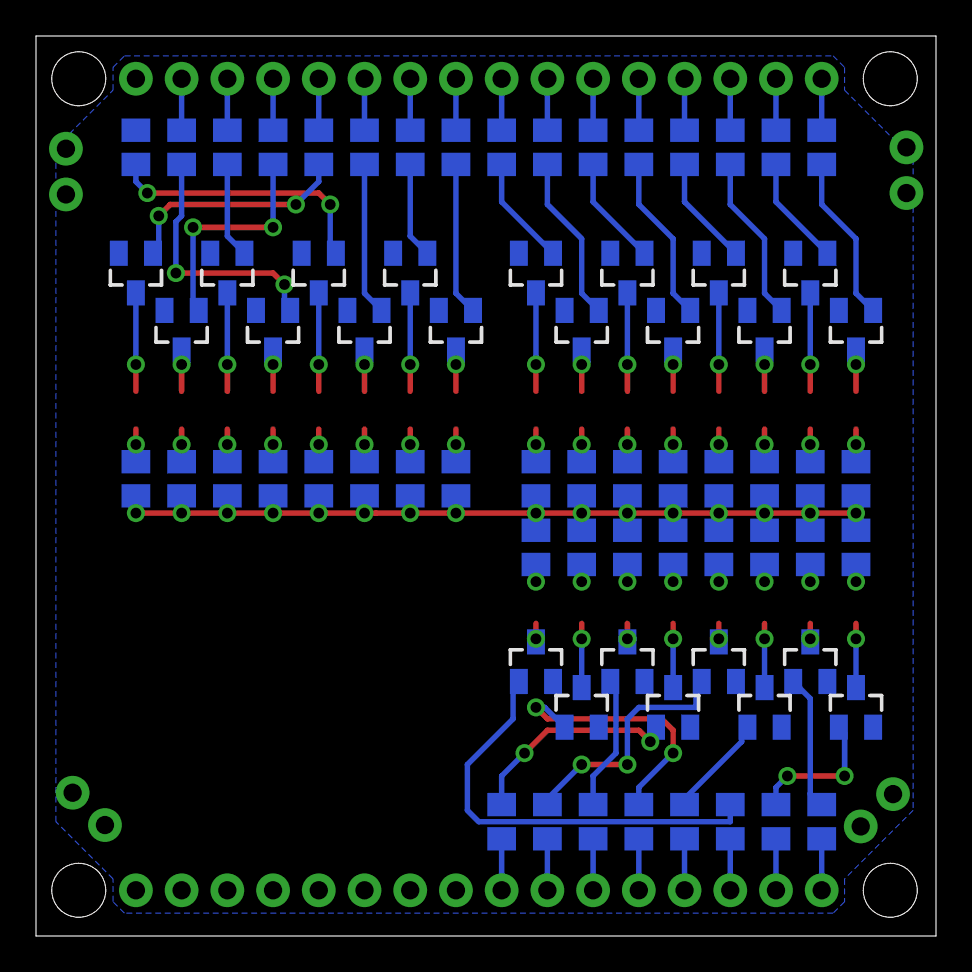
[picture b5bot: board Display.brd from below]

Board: 2 copper layers, 50.0 x 50.0 mm, 102 parts (72 on the bottom side), 98 nets.

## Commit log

2016-02-21 Adding RAM
    Add the 64K RAM/ROM
2016-02-21 Add CPU
    Add the CPU board
2016-02-21 Add MCU board
    add atmega 2560 as bootloader
2016-02-21 Add display
    Adding display status board (leds show signal levels on all the header
    pins).
2016-02-22 Add uart0 breakout
2016-02-22 Layout changes
2016-02-22 Fix up caps on ram/mcu board
2016-02-22 Update board outlines
    Adding white line around boards for de-panelization
2016-02-22 Create DIO board + fix MCU picture
2016-02-22 add RAM datasheet
2016-02-26 Route DIO Breakout + update Text
2016-02-26 Gerbers!
2016-03-10 Create Atmel Studio Project
2016-03-10 Expanding bus driver
    Added basic features to control the bus lines

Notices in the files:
parts and their libraries:
SparkFun-Connectors: Licensing: Creative Commons ShareAlike 4.0 International - https://creativecommons.org/licenses/by-sa/4.0
